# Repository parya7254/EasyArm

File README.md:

# EasyArm
An easy to build robot arm involving: 2 Servos, 2 RP2040s, an MPU 6500 Gyro Module, and 2 nRF24L01+ modules. This project is my submission for a guide for the kit-lab YSWS from Hack Club.

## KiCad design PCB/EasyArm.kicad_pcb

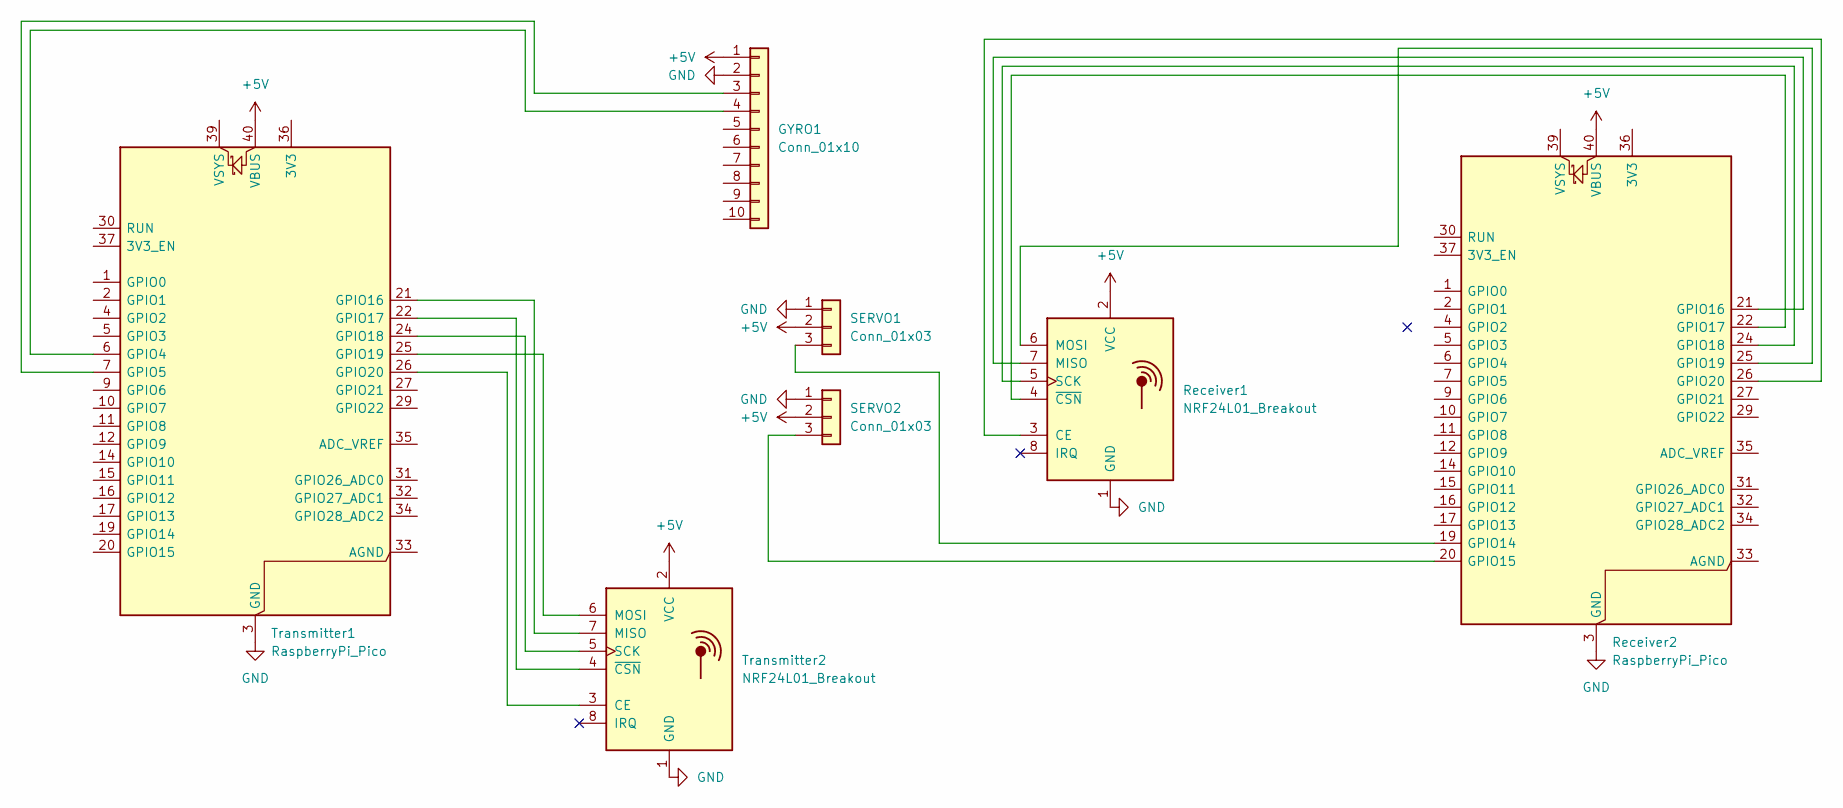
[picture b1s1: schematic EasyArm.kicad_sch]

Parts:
GYRO1: Conn_01x10; PinHeader_1x10_P2.54mm_Vertical
Receiver1: NRF24L01_Breakout; nRF24L01_Breakout
Receiver2: RaspberryPi_Pico; RaspberryPi_Pico_Common_Unspecified
SERVO1, SERVO2: Conn_01x03; PinHeader_1x03_P2.54mm_Vertical
Transmitter1: RaspberryPi_Pico; RaspberryPi_Pico_Common_Unspecified
Transmitter2: NRF24L01_Breakout; nRF24L01_Breakout

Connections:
+5V: GYRO1.1, Receiver1.2 (VCC), Receiver2.40 (VBUS), SERVO1.2, SERVO2.2, Transmitter1.40 (VBUS), Transmitter2.2 (VCC)
GND: GYRO1.2, Receiver1.1 (GND), Receiver2.3 (GND), Receiver2.8 (GND), Receiver2.13 (GND), Receiver2.18 (GND), Receiver2.23 (GND), Receiver2.28 (GND), Receiver2.38 (GND), SERVO1.1, SERVO2.1, Transmitter1.3 (GND), Transmitter1.8 (GND), Transmitter1.13 (GND), Transmitter1.18 (GND), Transmitter1.23 (GND), Transmitter1.28 (GND), Transmitter1.38 (GND), Transmitter2.1 (GND)
unnamed: GYRO1.3, Transmitter1.7 (GPIO5)
unnamed: GYRO1.4, Transmitter1.6 (GPIO4)
unnamed: Receiver1.3 (CE), Receiver2.26 (GPIO20)
unnamed: Receiver1.7 (MISO), Receiver2.21 (GPIO16)
unnamed: Receiver1.6 (MOSI), Receiver2.25 (GPIO19)
unnamed: Receiver1.5 (SCK), Receiver2.24 (GPIO18)
unnamed: Receiver1.4 (~CSN), Receiver2.22 (GPIO17)
unnamed: Receiver2.19 (GPIO14), SERVO1.3
unnamed: Receiver2.20 (GPIO15), SERVO2.3
unnamed: Transmitter1.21 (GPIO16), Transmitter2.7 (MISO)
unnamed: Transmitter1.22 (GPIO17), Transmitter2.4 (~CSN)
unnamed: Transmitter1.24 (GPIO18), Transmitter2.5 (SCK)
unnamed: Transmitter1.25 (GPIO19), Transmitter2.6 (MOSI)
unnamed: Transmitter1.26 (GPIO20), Transmitter2.3 (CE)

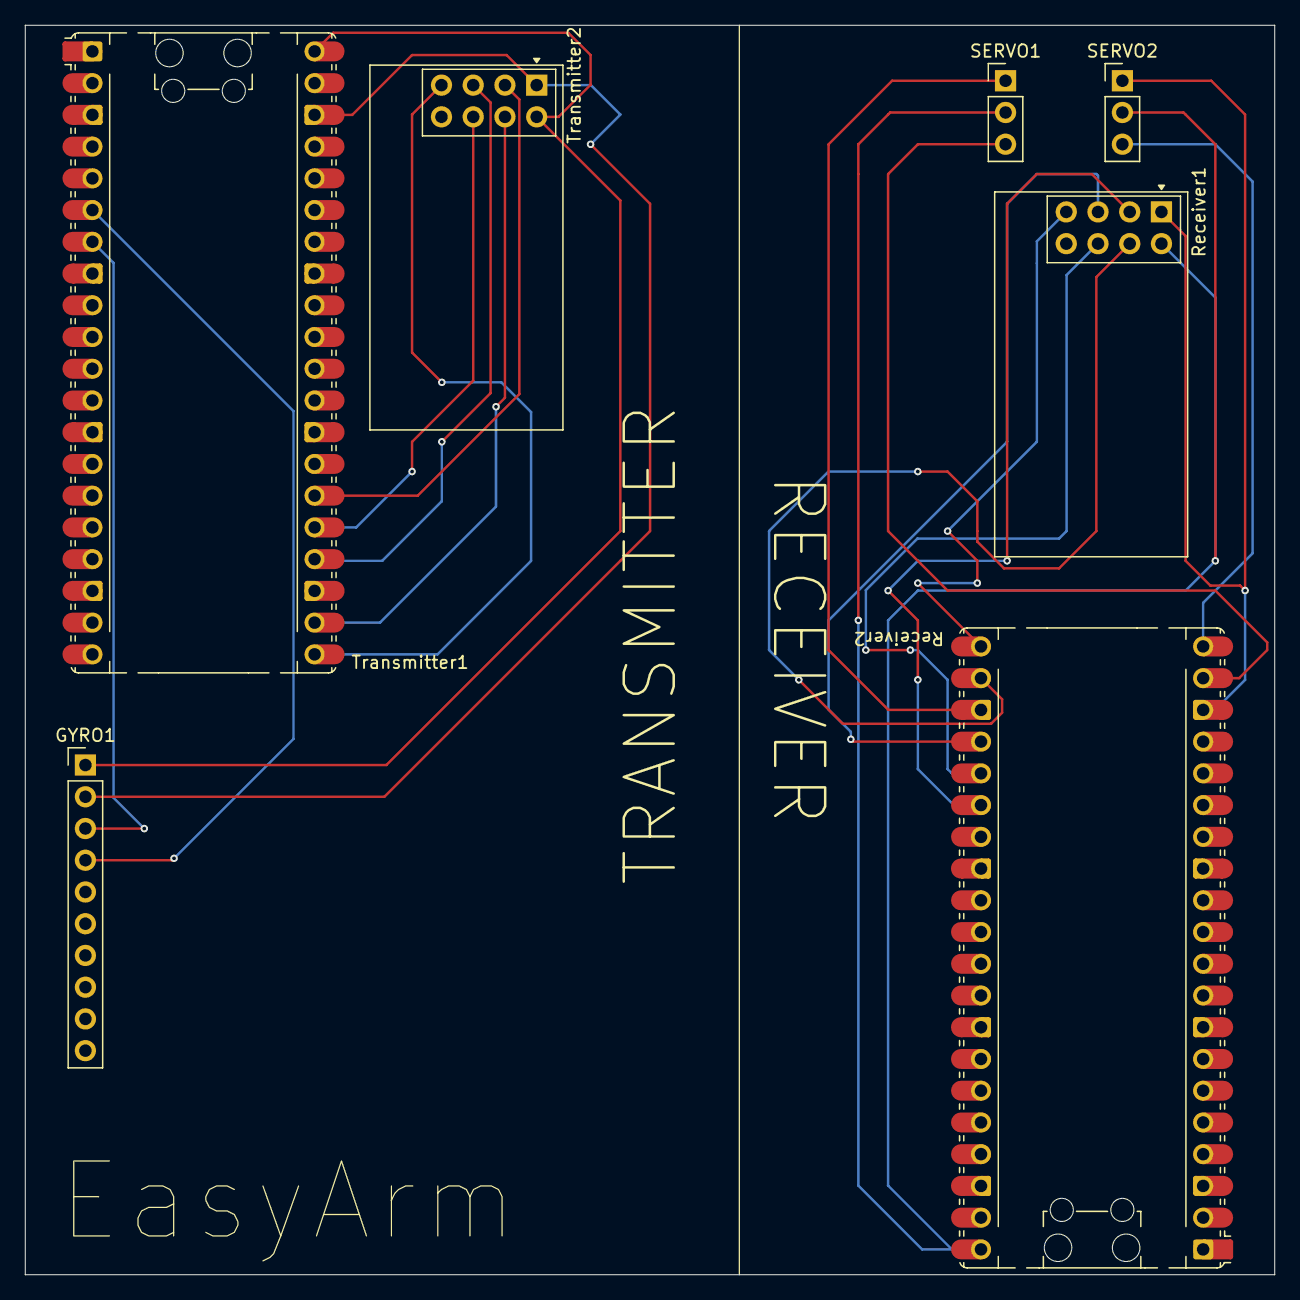
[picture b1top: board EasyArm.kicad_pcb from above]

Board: 2 copper layers, 100.0 x 100.0 mm, 7 parts (0 on the bottom side), 16 nets.

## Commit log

2026-03-13 Create GUIDE.md for mini robot arm project
    Added a guide for building a custom wirelessly controlled robot arm with parts list.
2026-03-13 Expand schematic creation instructions in GUIDE.md
    Added detailed instructions for creating a schematic using KiCad, including component selection and placement.
2026-03-13 Add initial schematic details and project progress
    Documented initial schematic layout and connections for the project, including details on components used and progress on the guide.
2026-03-13 add image
2026-03-13 Finished Whole Schematic Section
2026-03-13 Add finished schematic image to GUIDE.md
2026-03-13 Added Assign Footprints to guide
    Now we are finished with the schematic part.
2026-03-14 Create placeholder
2026-03-14 Rename GUIDE.md to Guide/GUIDE.md
2026-03-14 Rename image-1.png to Guide/image-1.png
2026-03-14 Rename image-10.png to Guide/image-10.png
2026-03-14 Rename image-11.png to Guide/image-11.png
2026-03-14 Rename image-2.png to Guide/image-2.png
2026-03-14 Rename image-3.png to Guide/image-3.png
2026-03-14 Rename image-4.png to Guide/image-4.png
2026-03-14 Rename image-5.png to Guide/image-5.png
2026-03-14 Rename image-6.png to Guide/image-6.png
2026-03-14 Rename image-7.png to Guide/image-7.png
2026-03-14 Rename image-8.png to Guide/image-8.png
2026-03-14 Rename image-9.png to Guide/image-9.png
2026-03-14 Rename image.png to Guide/image.png
2026-03-14 Rename image-12.png to Guide/image-12.png
2026-03-14 Rename image-13.png to Guide/image-13.png
2026-03-14 Rename image-14.png to Guide/image-14.png
2026-03-14 Moved journal and images to folder
2026-03-17 Finished PCB {art of Guide
2026-03-17 Added part about wiring traces
2026-03-19 Finished PCB Routing Part
2026-03-19 Added Journal for Day 3
2026-03-19 Rename EasyArm.kicad_pcb to PCB/EasyArm.kicad_pcb
2026-03-19 Rename EasyArm.kicad_pro to PCB/EasyArm.kicad_pro
2026-03-19 Rename EasyArm.kicad_sch to PCB/EasyArm.kicad_sch
2026-03-20 Finished PCB part of guide
2026-04-08 Started Creating Transmitter's Case and did Guide
